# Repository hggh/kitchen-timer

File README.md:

# kitchen-timer

## parts

 * Atmel 328p (1Mhz, BOD disabled)
 * 32 khz crystal (timer2, async)
 * TM1637 – 4 Digit 7 Segment Display
 * Rotary encoder KY-040
 * TP4056 with DW01-P
 * LiPo 18650
 * buzzer
 
## BOM

| Qty |typ|
|--------|-------|
| 3  | 100nf smd 0805 |
| 2  | 10µF smd 0805 |
| 1  | TP4056 |
| 2 | BC817 |
| 1 | BC807|
| 2 | 10k smd 0805 |
| 3 | 2.6k smd 0805|
| 1 | 0.4 smd 1206
| 1 | 20k smd 0805 |
| 1 | 2k smd 0805 |
| 1 | 100 smd 0805 |
|1 | 1k smd 0805|
| 2 | 4.7k smd 0805 |
| 1 | ATmega 328-PU |
| 1 | FS8025A |
| 1 | DW01A |
| 1 | 32khz crystal |
| 1 | KY-040 |
| 1 | battery holder 18650 |
| 1 | lipo 18650|

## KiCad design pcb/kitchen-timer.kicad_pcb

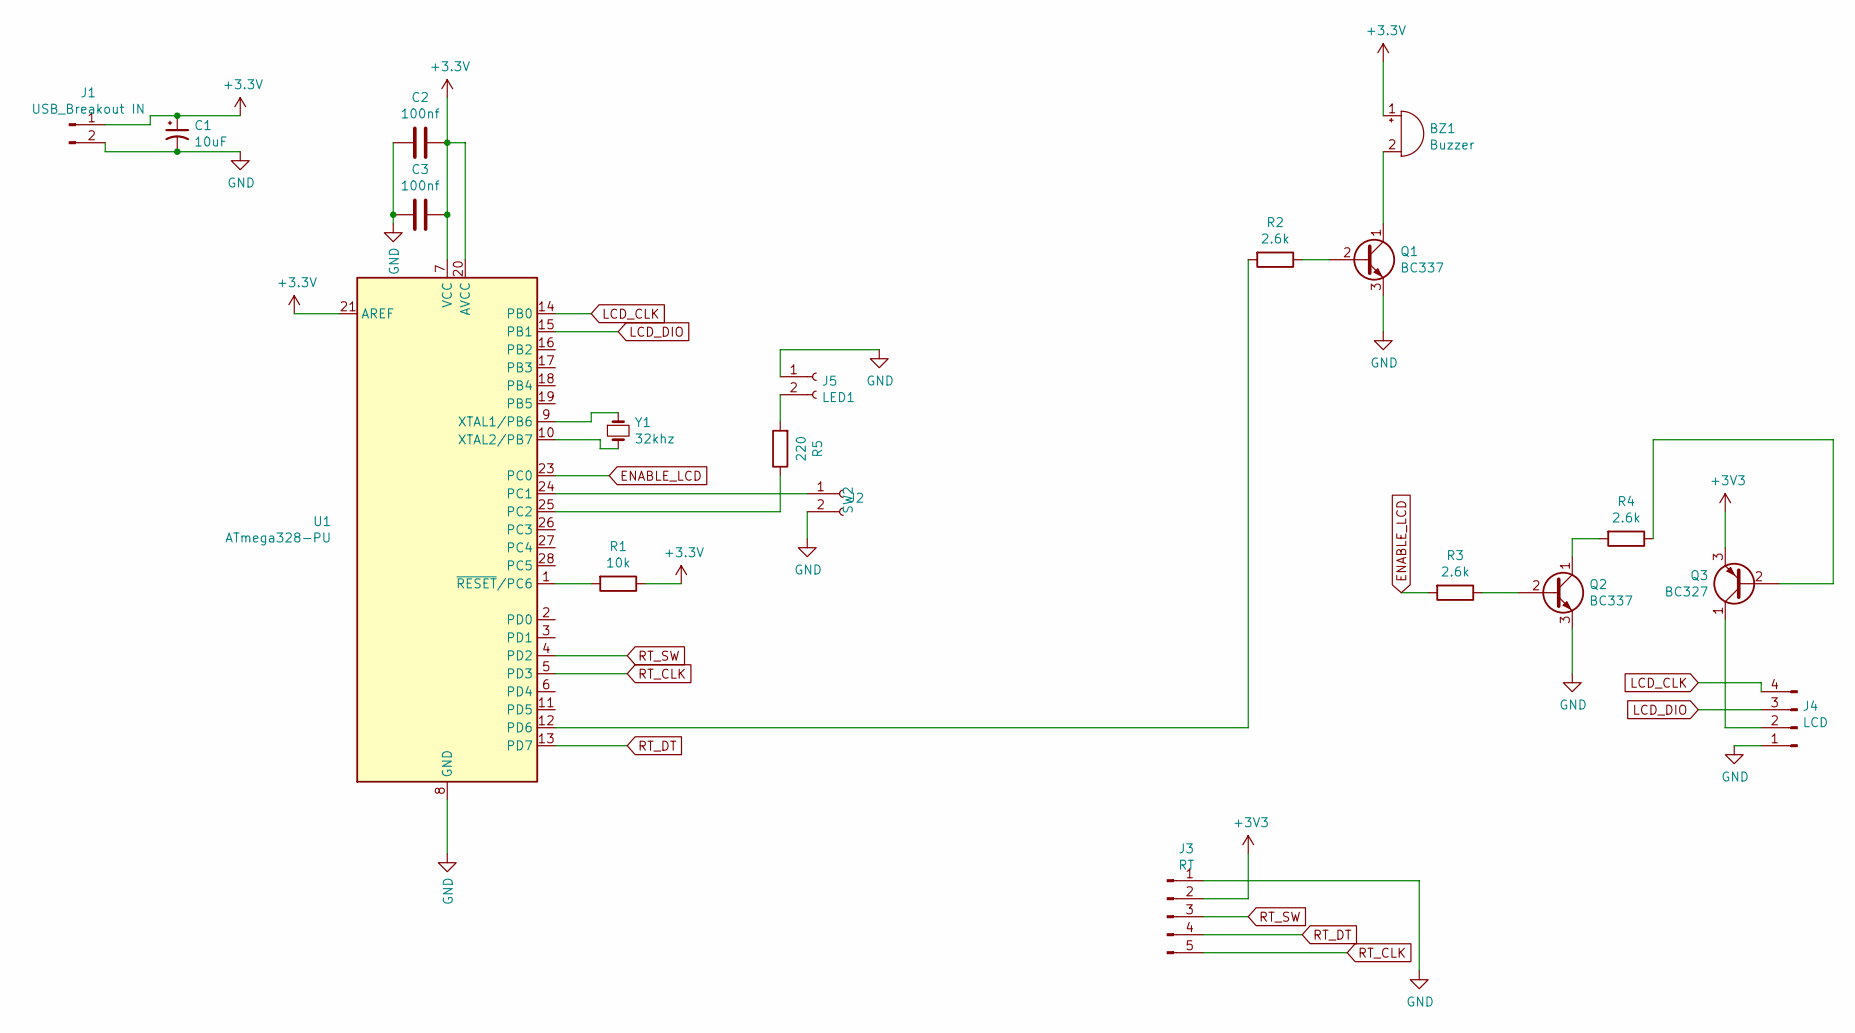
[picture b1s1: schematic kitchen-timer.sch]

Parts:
BZ1: Buzzer; PinHeader_1x02_P2.00mm_Vertical
C1: 10uF; CP_Radial_D4.0mm_P2.00mm
C2, C3: 100nf; C_0805_2012Metric_Pad1.15x1.40mm_HandSolder
J1: USB_Breakout IN; PinHeader_1x02_P2.00mm_Vertical
J2: SW2; PinHeader_1x02_P2.00mm_Vertical
J3: RT; PinHeader_1x05_P2.54mm_Vertical
J4: LCD; PinHeader_1x04_P2.54mm_Vertical
J5: LED1; PinHeader_1x02_P2.00mm_Vertical
Q1, Q2: BC337; TO-92_Inline
Q3: BC327; TO-92_Inline
R1: 10k; R_0805_2012Metric_Pad1.15x1.40mm_HandSolder
R2, R3, R4: 2.6k; R_0805_2012Metric_Pad1.15x1.40mm_HandSolder
R5: 220; R_Axial_DIN0207_L6.3mm_D2.5mm_P10.16mm_Horizontal
U1: ATmega328-PU; DIP-28_W7.62mm
Y1: 32khz; Crystal_DS15_D1.5mm_L5.0mm_Vertical

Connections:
ENABLE_LCD: R3.2, U1.23 (PC0)
GND: C1.2, C2.2, C3.2, J1.2, J2.2, J3.1, J4.1, J5.1, Q1.3 (E), Q2.3 (E), U1.8 (GND), U1.22 (GND)
LCD_CLK: J4.4, U1.14 (PB0)
LCD_DIO: J4.3, U1.15 (PB1)
unnamed: BZ1.2 (+), Q1.1 (C)
unnamed: J2.1, U1.24 (PC1)
unnamed: J4.2, Q3.1 (C)
unnamed: J5.2, R5.2
unnamed: Q1.2 (B), R2.1
unnamed: Q2.1 (C), R4.2
unnamed: Q2.2 (B), R3.1
unnamed: Q3.2 (B), R4.1
unnamed: R1.2, U1.1 (~RESET~/PC6)
unnamed: R2.2, U1.12 (PD6)
unnamed: R5.1, U1.25 (PC2)
unnamed: U1.9 (XTAL1/PB6), Y1.1
unnamed: U1.10 (XTAL2/PB7), Y1.2
RT_CLK: J3.5, U1.5 (PD3)
RT_DT: J3.4, U1.13 (PD7)
RT_SW: J3.3, U1.4 (PD2)

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
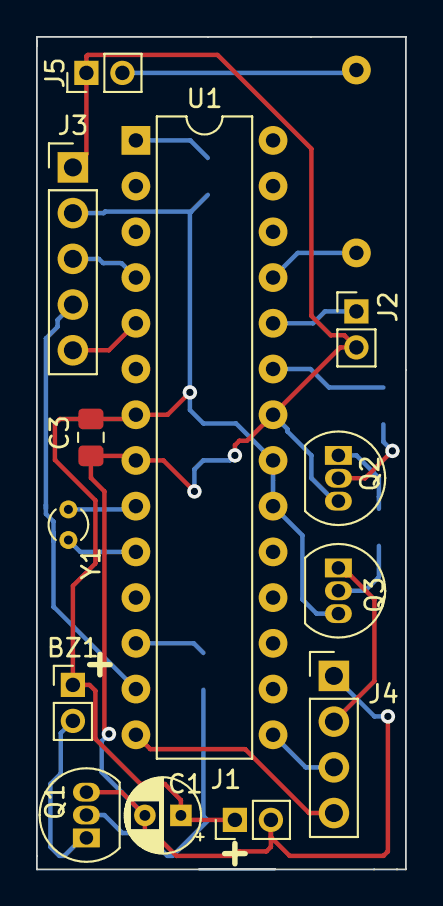
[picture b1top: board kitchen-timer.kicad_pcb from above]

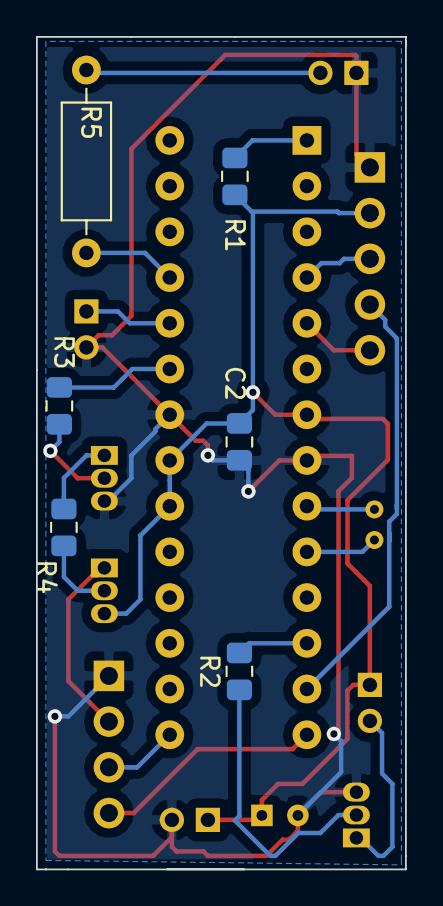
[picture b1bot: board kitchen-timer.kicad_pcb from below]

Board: 2 copper layers, 20.5 x 46.2 mm, 19 parts (6 on the bottom side), 21 nets.

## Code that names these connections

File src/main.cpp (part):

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#include <Menu7Seg.h>

#define BUZZER_PIN 6
#define RT_SW 2
#define RT_CLK 3
#define RT_DT 7
#define DISPLAY_CLK A5
#define DISPLAY_DIO A4
#define ENABLE_LCD 5

#define TP4056_PIN_STDBY A3
#define TP4056_PIN_CHRG A2
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  power_spi_disable();
  power_twi_disable();

  pinMode(RT_CLK, INPUT_PULLUP);
  pinMode(RT_DT, INPUT_PULLUP);
  pinMode(RT_SW, INPUT_PULLUP);
  pinMode(BUZZER_PIN, INPUT);

  pinMode(ENABLE_LCD, OUTPUT);
  enable_display();

  debouncer.attach(RT_SW);
  debouncer.interval(25);

  attachInterrupt(digitalPinToInterrupt(RT_CLK), rt_int_clk, CHANGE);
  attachInterrupt(digitalPinToInterrupt(RT_SW), rt_int_sw, FALLING);

  wakeup_time = millis();

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
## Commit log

2019-10-05 add 328 1Mhz, BOD disabled
2019-10-05 add atmel, attiny 85 as two few pins use a 328
2019-10-26 add code
2019-10-27 add pcb
2019-10-28 added gnd plane on back
2019-10-30 added case
2019-10-30 added wood case test
2019-11-05 more designs
2019-11-05 new case
2019-11-05 case update
2019-11-10 micro usb breakout
2019-11-10 update case
2019-11-13 updated case
2019-11-13 update case with usb connector
2019-11-15 use 32khz
2019-11-16 play sound via delay; tone uses timer2
2019-11-16 add splitted case for better printing
2019-11-17 cleanup cases; add 1.0
2019-11-17 going to dip version, because of 32k crystel
2019-11-17 old version
2019-11-22 enable/display display
2019-11-22 remember last start pos; update rotery encoder code
2019-11-29 add base plate
2019-12-03 display: size
2019-12-23 add pics
2020-01-14 add beep if timer stars; longer press
2020-04-23 check battery level before activating timer and warn if too low
2020-05-20 changed to openscad library
    https://github.com/hggh/openscad-utils
2021-04-30 Add menu library
2021-04-30 enable menu with settings: set time how long the timer will beep
2022-04-23 update case with prismoid function
2022-05-01 add splitted parts new case with USB-C
2022-05-01 add pic
2022-05-10 update floor plate for new site
2022-05-23 new pcb with tp4056 on the same pcb
2022-07-29 reformat ini
2022-07-30 update tp4056 charge load
2022-07-30 display tp4056 status
2022-08-08 update stls
2023-04-03 regenerate
2023-04-03 add Prusa
2023-04-03 removed old pcb
2023-04-03 Kicad 6
2023-04-03 update pic
